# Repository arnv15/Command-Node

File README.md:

# Command Node

A fully custom 3D printed macropad built from scratch with a 3×3 key grid, rotary encoder, and OLED display.

## Features

- 9x Cherry MX switches in a 3×3 layout
- EC11 rotary encoder (volume control + OS toggle click)
- 0.91" 128×32 SSD1306 OLED display showing name and current OS layer
- Dual OS support — toggle between Windows and Mac layouts instantly
- KMK firmware written in CircuitPython (no compiling needed!)
- 3D printed case with heat-set inserts
- Seeed XIAO RP2040 microcontroller

## Overall Design

The macropad features a compact 3×3 key layout with the rotary encoder and OLED display across the top. The USB-C port is accessible from the right side. The two-part 3D printed case is held together with M3 screws and heat-set inserts.

## PCB

| **Schematic**                      | **PCB Layout**         |
| ---------------------------------- | ---------------------- |
|  |  |

The PCB was designed in KiCad. The switch matrix uses COL2ROW diode direction with 1N4148 diodes. The OLED connects via I2C on SDA/SCL pins, and the EC11 encoder click is wired as a direct pin (no diode needed).

- [x] I ran DRC and there are 0 errors

## CAD

The case is two-part and 3D printed. The top shell holds the switches, encoder, and OLED in place, while the bottom shell houses the PCB. Everything is secured with 4x M3x16mm screws threading into M3x5x4mm heat-set inserts pressed into the bottom shell.

[OnShape Link](https://cad.onshape.com/documents/35dce9458257a454ca9a87ec/w/10d574b05dc610b688c542cb/e/8b960576cf94807eaae72969)

## Firmware

Written using **KMK** (CircuitPython) — no compiling or flashing needed after the initial CircuitPython setup. Just edit `code.py` on the `CIRCUITPY` drive and it reloads automatically.

**Key layout:**

```
[ Prev  ] [ Play  ] [ Next  ]
[ Ctrl+Z] [ Ctrl+C] [ Ctrl+V]
[ Scrnsh] [ Sleep ] [ Scrnsvr]
         [Enc Click = OS Toggle]
```

**Encoder rotation:** Volume down / Volume up

**OS Toggle:** Pressing the encoder switches between Windows mode (Ctrl shortcuts, Print Screen) and Mac mode (Cmd shortcuts, Cmd+Shift+4 screenshot). The OLED updates to show the current OS.

**OLED display:** Shows name and current active OS layer dynamically.

You can find the full `main.py` in the `firmware/` folder of this repo.

## BOM

| Part                             | Quantity | Notes                                     |
| -------------------------------- | -------- | ----------------------------------------- |
| Seeed XIAO RP2040                | 1        | Microcontroller                           |
| Cherry MX Switches               | 9        | Any MX-compatible switch                  |
| 1N4148 Diodes (through-hole)     | 10       | 9 for switch matrix + 1 for encoder click |
| EC11 Rotary Encoder              | 1        | With push-click                           |
| 0.91" SSD1306 OLED (128×32, I2C) | 1        | Pin order: GND-VCC-SCL-SDA                |
| DSA Keycaps                      | 9        | White blank                               |
| M3x16mm Screws                   | 4        | For case assembly                         |
| M3x5x4mm Heat-set Inserts        | 4        | Press into bottom shell                   |
| PCB                              | 1        | Custom KiCad design                       |
| 3D Printed Case (top + bottom)   | 1 set    | PLA or PETG                               |

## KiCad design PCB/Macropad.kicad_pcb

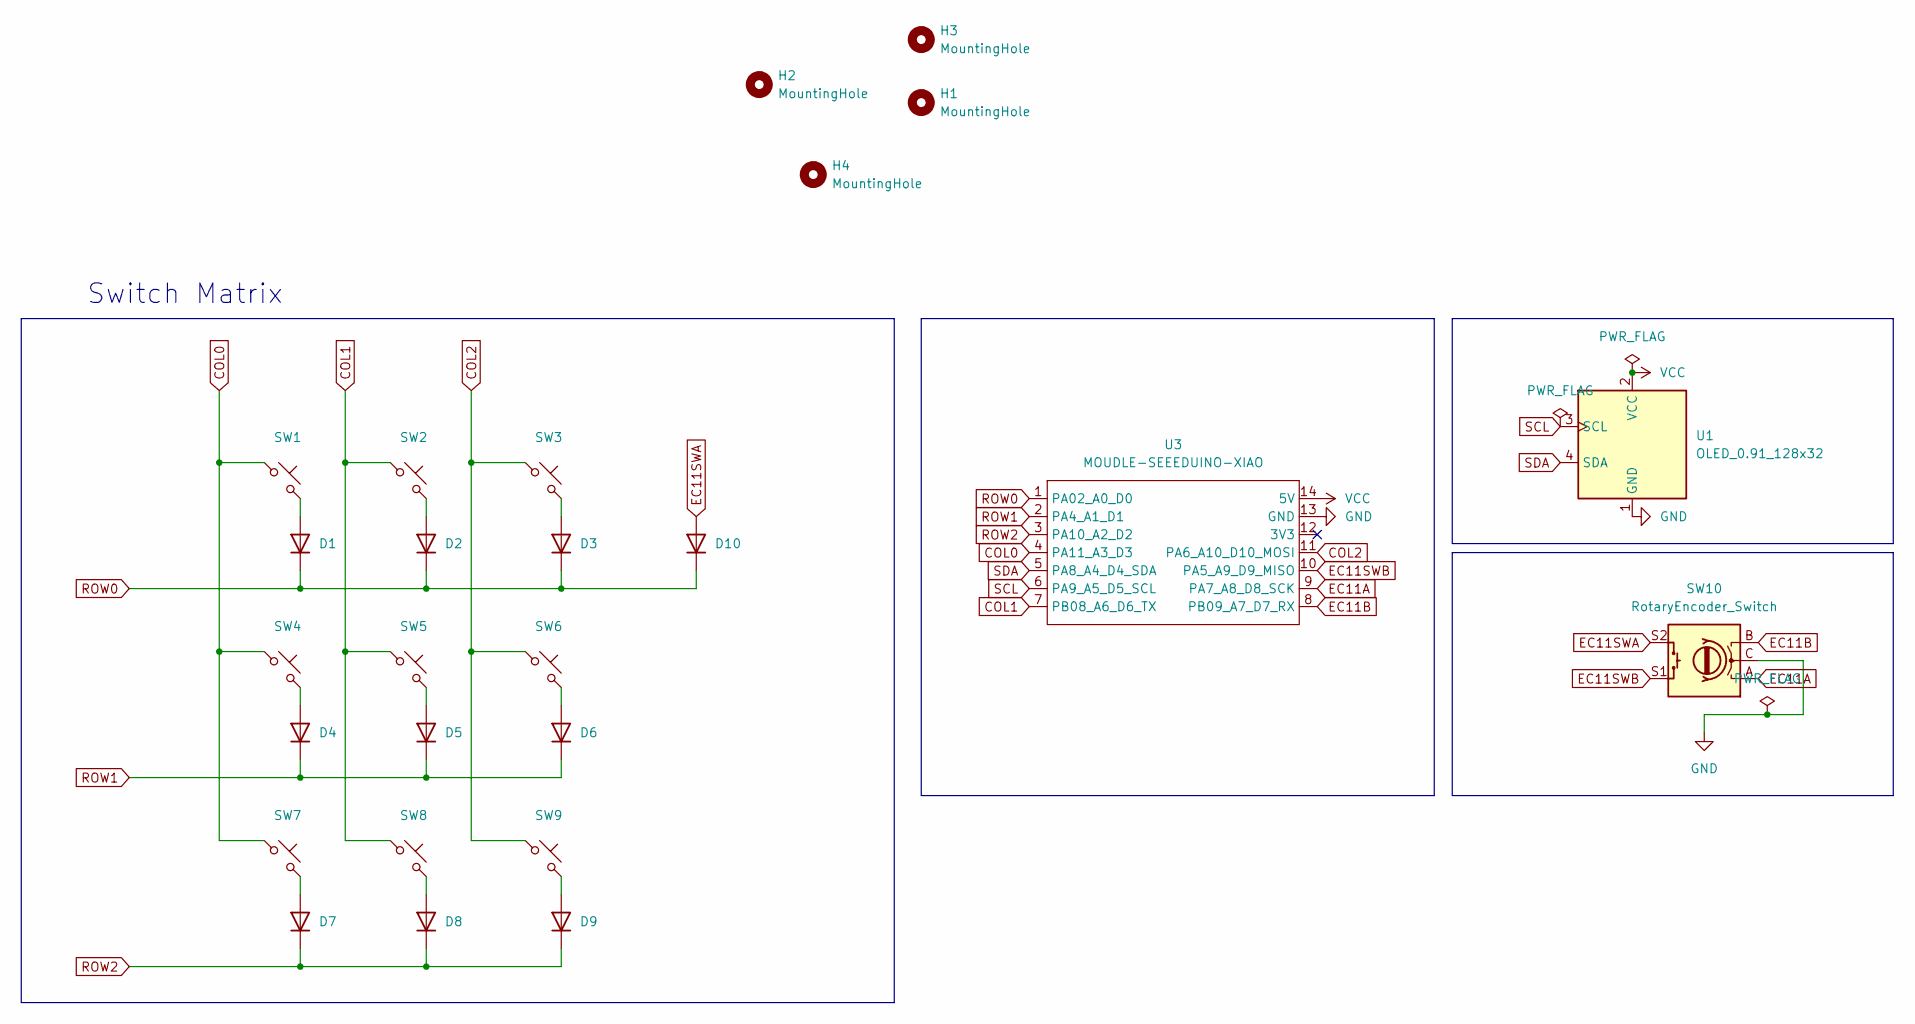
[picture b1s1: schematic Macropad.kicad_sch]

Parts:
D1, D2, D3, D4, D5, D6, D7, D8, D9, D10: 1N4148; D_DO-35_SOD27_P7.62mm_Horizontal
H1, H2, H3, H4: MountingHole; MountingHole_3.2mm_M3
SW1, SW2, SW3, SW4, SW5, SW6, SW7, SW8, SW9: SW_Push_45deg; SW_Cherry_MX_1.00u_PCB
SW10: RotaryEncoder_Switch; RotaryEncoder_Alps_EC11E-Switch_Vertical_H20mm
U1: OLED_0.91_128x32; SSD1306-0.91-OLED-4pin-128x32
U3: MOUDLE-SEEEDUINO-XIAO; XIAO-Generic-Hybrid-14P-2.54-21X17.8MM

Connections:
COL0: SW1.1, SW4.1, SW7.1, U3.4 (PA11_A3_D3)
COL1: SW2.1, SW5.1, SW8.1, U3.7 (PB08_A6_D6_TX)
COL2: SW3.1, SW6.1, SW9.1, U3.11 (PA6_A10_D10_MOSI)
EC11A: SW10.A, U3.9 (PA7_A8_D8_SCK)
EC11B: SW10.B, U3.8 (PB09_A7_D7_RX)
EC11SWA: D10.2 (A), SW10.S2
EC11SWB: SW10.S1, U3.10 (PA5_A9_D9_MISO)
GND: SW10.C, U1.1 (GND), U3.13 (GND)
unnamed: D1.2 (A), SW1.2
unnamed: D2.2 (A), SW2.2
unnamed: D3.2 (A), SW3.2
unnamed: D4.2 (A), SW4.2
unnamed: D5.2 (A), SW5.2
unnamed: D6.2 (A), SW6.2
unnamed: D7.2 (A), SW7.2
unnamed: D8.2 (A), SW8.2
unnamed: D9.2 (A), SW9.2
ROW0: D1.1 (K), D2.1 (K), D3.1 (K), D10.1 (K), U3.1 (PA02_A0_D0)
ROW1: D4.1 (K), D5.1 (K), D6.1 (K), U3.2 (PA4_A1_D1)
ROW2: D7.1 (K), D8.1 (K), D9.1 (K), U3.3 (PA10_A2_D2)
SCL: U1.3 (SCL), U3.6 (PA9_A5_D5_SCL)
SDA: U1.4 (SDA), U3.5 (PA8_A4_D4_SDA)
VCC: U1.2 (VCC), U3.14 (5V)

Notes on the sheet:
Switch Matrix

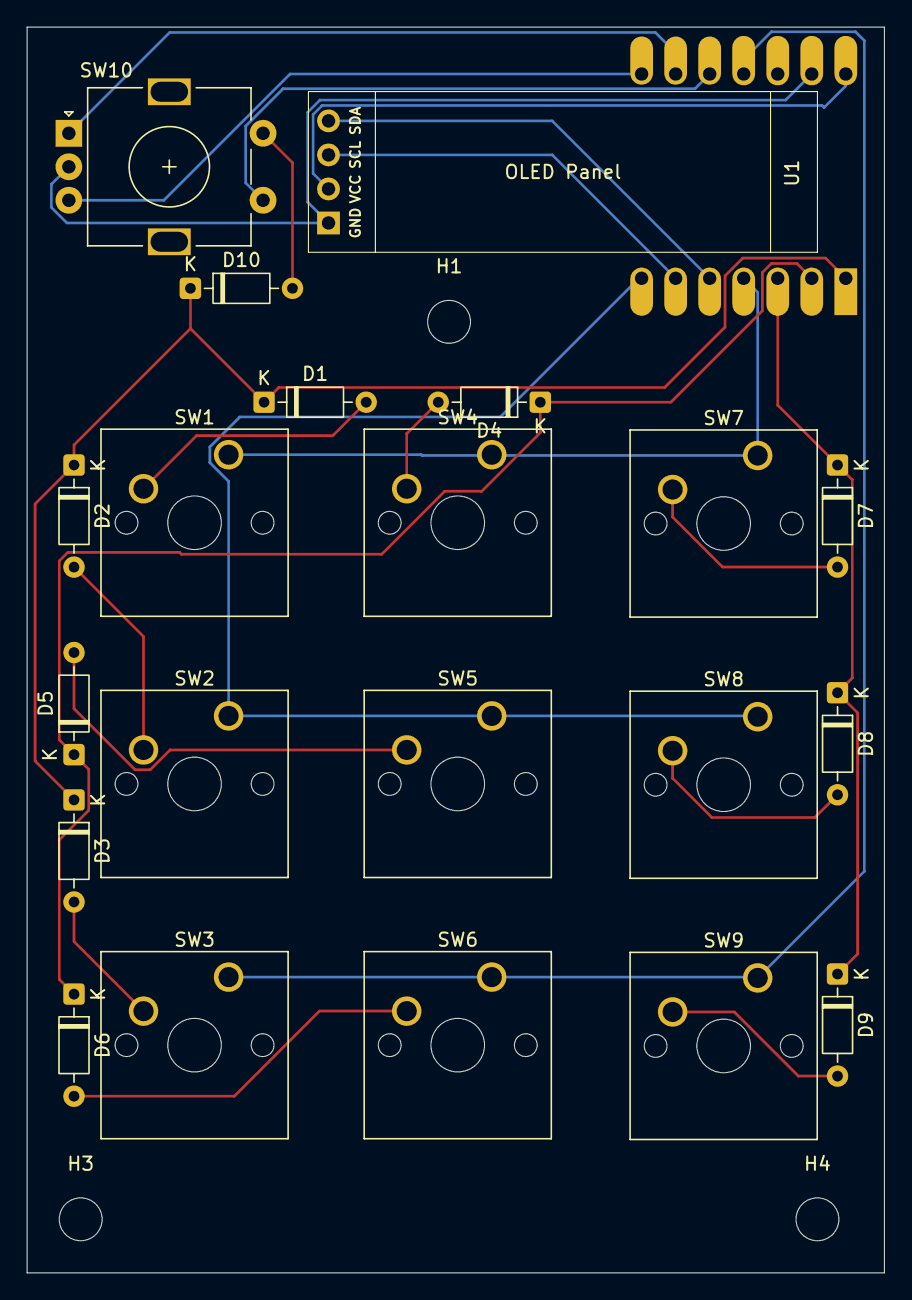
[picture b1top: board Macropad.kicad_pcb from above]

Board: 2 copper layers, 64.0 x 93.0 mm, 25 parts (1 on the bottom side), 23 nets.

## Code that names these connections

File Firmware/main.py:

import board
from kmk.kmk_keyboard import KMKKeyboard
from kmk.keys import KC
from kmk.modules.layers import Layers
from kmk.modules.encoder import EncoderHandler
from kmk.extensions.media_keys import MediaKeys
from kmk.extensions.oled import Oled, OledDisplayMode, OledReactionType
from kmk.hid import HIDModes
from kmk.scanners.keypad import MatrixScanner
from kmk.scanners.digitalio import KeysScanner

keyboard = KMKKeyboard()
keyboard.extensions.append(MediaKeys())
 
layers_ext = Layers()
keyboard.modules.append(layers_ext)

# MATRIX
keyboard.matrix = MatrixScanner(
    column_pins=(board.D3, board.D6, board.D10),  # COL0, COL1, COL2
    row_pins=(board.D0, board.D1, board.D2),       # ROW0, ROW1, ROW2
    columns_to_anodes=True,                         # COL2ROW diode direction
)

# ENCODER CLICK
encoder_click = KeysScanner(
    pins=(board.D9,),  # EC11SWA on GP4 = D9 on XIAO
)
keyboard.matrix = [keyboard.matrix, encoder_click]

# ENCODER ROTATION
encoder_handler = EncoderHandler()
encoder_handler.pins = ((board.D8, board.D7, None),)  # A=GP2, B=GP1, no push pin

encoder_handler.map = [
    ((KC.VOLD, KC.VOLU),),  # Windows
    ((KC.VOLD, KC.VOLU),),  # Mac
]
keyboard.modules.append(encoder_handler)


# Shortcut to toggle between layers
TOGGLE_OS = KC.TG(1)

keyboard.keymap = [

    # Windows
    [
        KC.MPRV,           KC.MPLY,           KC.MNXT,   
        KC.LCTL(KC.Z),     KC.LCTL(KC.C),     KC.LCTL(KC.V), 
        KC.PSCR,           KC.SLEP,           KC.SCRL,   
        TOGGLE_OS,                                   
    ],

    #Mac
    [
        KC.MPRV,                    KC.MPLY,              KC.MNXT,   
        KC.LGUI(KC.Z),              KC.LGUI(KC.C),        KC.LGUI(KC.V), 
        KC.LGUI(KC.LSFT(KC.N4)),    KC.SLEP,              KC.SCRL,   
        TOGGLE_OS,                                                   
    ],
]

# OLED DISPLAY
oled_ext = Oled(
    OledDisplayMode.TXT,
    toDisplay="Command Node",
    flip=False,
)
keyboard.extensions.append(oled_ext)

# START
if __name__ == '__main__':
    keyboard.run()

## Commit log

2026-03-18 Added CAD, PCB, Production files
2026-03-22 Fix images in README
2026-03-23 Fix onshape link
